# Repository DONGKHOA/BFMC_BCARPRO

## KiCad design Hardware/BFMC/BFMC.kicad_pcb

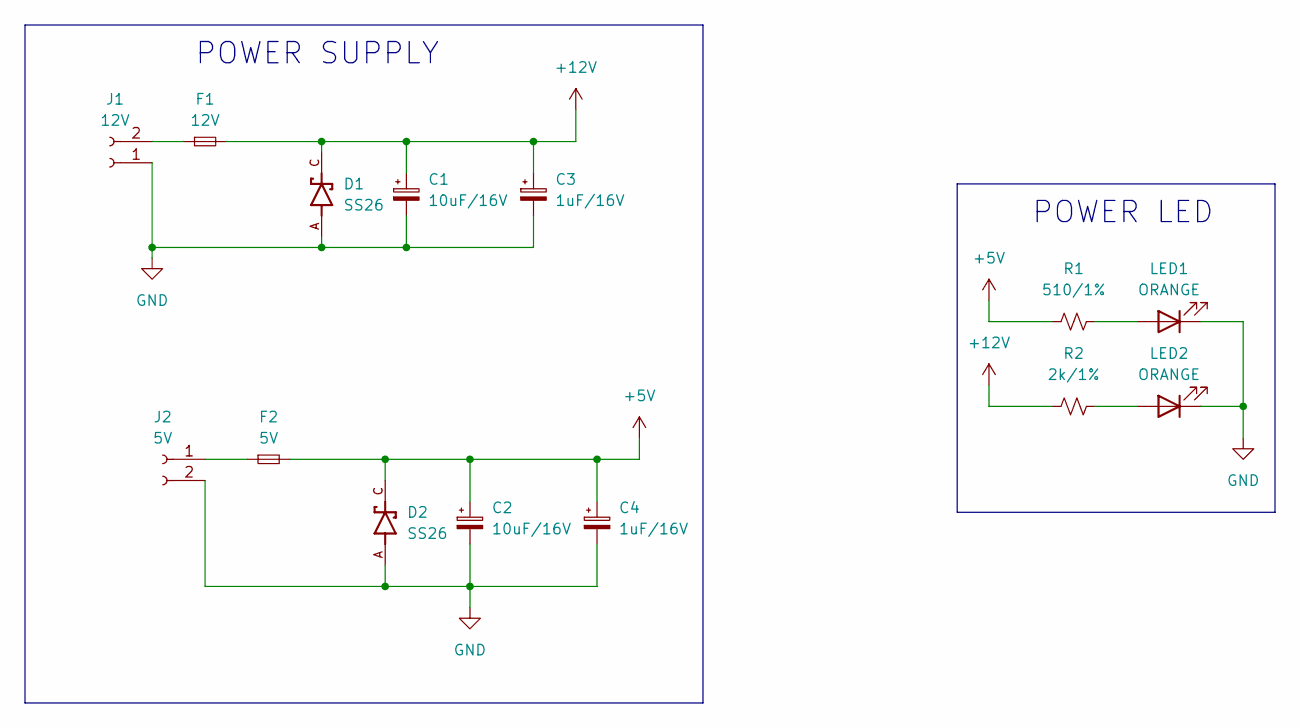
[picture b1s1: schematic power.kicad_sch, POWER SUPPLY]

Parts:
C1, C2: 10uF/16V; CP_Elec_4x5.4
C3, C4: 1uF/16V; CP_Elec_4x5.4
D1, D2: SS26; DIOM4325X250N
F1: 12V; Fuse_1812_4532Metric_Pad1.30x3.40mm_HandSolder
F2: 5V; Fuse_1812_4532Metric_Pad1.30x3.40mm_HandSolder
J1: 12V; au_XH_2.54mm_2_Chan_Dan_SMD_Nam_Ngang
J2: 5V; TerminalBlock_MetzConnect_Type073_RT02602HBLU_1x02_P5.08mm_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
LED1, LED2: ORANGE; LED_1206_3216Metric_Pad1.42x1.75mm_HandSolder
R1: 510/1%; R_0603_1608Metric_Pad0.98x0.95mm_HandSolder
R2: 2k/1%; R_0603_1608Metric_Pad0.98x0.95mm_HandSolder

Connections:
+5V: C2.1, C4.1, D2.C, F2.2, R1.1; also elsewhere on the board
+12V: C1.1, C3.1, D1.C, F1.2, R2.1; also elsewhere on the board
GND: C1.2, C2.2, C3.2, C4.2, D1.A, D2.A, J1.1, J2.2, LED1.1 (K), LED2.1 (K); also elsewhere on the board
unnamed: F1.1, J1.2
unnamed: F2.1, J2.1
unnamed: LED1.2 (A), R1.2
unnamed: LED2.2 (A), R2.2

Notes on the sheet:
POWER SUPPLY
POWER LED

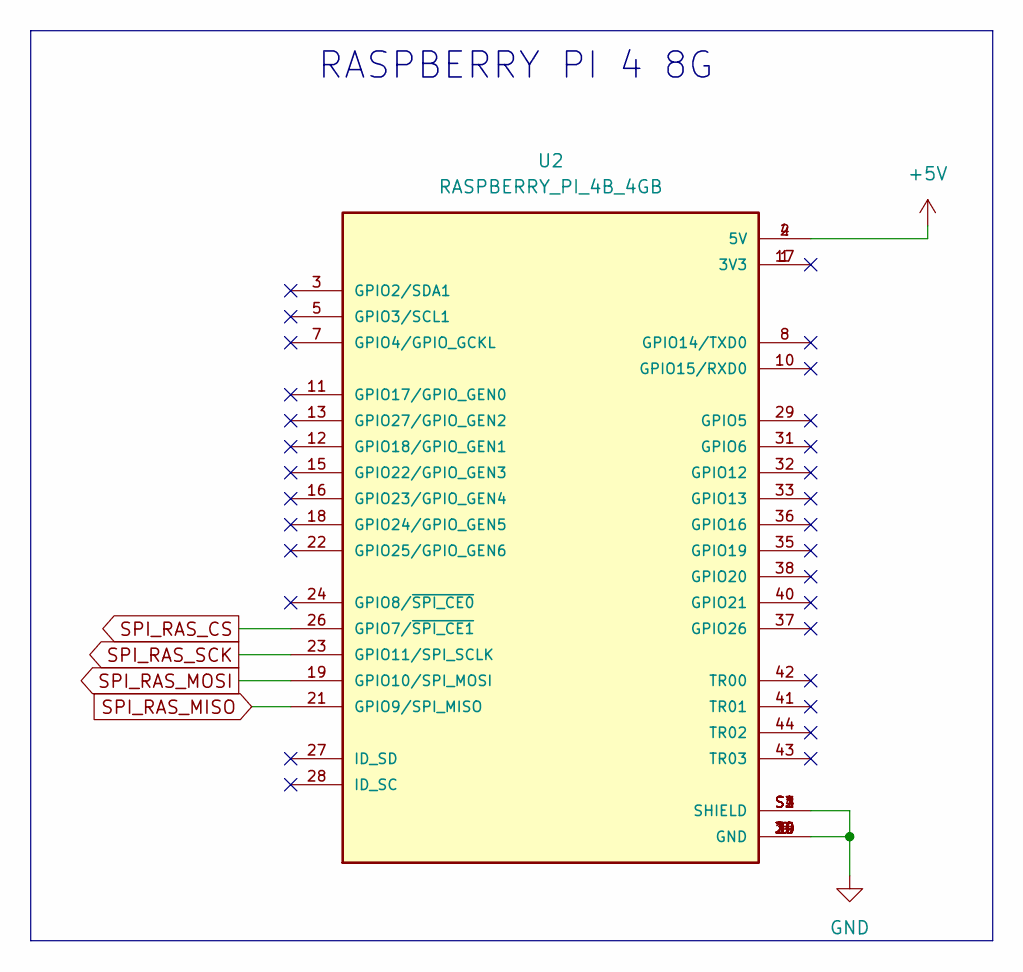
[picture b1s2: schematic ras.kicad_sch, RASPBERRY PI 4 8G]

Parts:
U2: RASPBERRY_PI_4B_4GB; MODULE_RASPBERRY_PI_4B_4GB; PARTREV 4

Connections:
+5V: U2.2 (5V), U2.4 (5V); also elsewhere on the board
GND: U2.6 (GND), U2.9 (GND), U2.14 (GND), U2.20 (GND), U2.25 (GND), U2.30 (GND), U2.34 (GND), U2.39 (GND), U2.S1 (SHIELD), U2.S2 (SHIELD), U2.S3 (SHIELD), U2.S4 (SHIELD); also elsewhere on the board
SPI_RAS_CS: U2.26 (GPIO7/~SPI_CE1); also elsewhere on the board
SPI_RAS_MISO: U2.21 (GPIO9/SPI_MISO); also elsewhere on the board
SPI_RAS_MOSI: U2.19 (GPIO10/SPI_MOSI); also elsewhere on the board
SPI_RAS_SCK: U2.23 (GPIO11/SPI_SCLK); also elsewhere on the board

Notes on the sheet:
RASPBERRY PI 4 8G

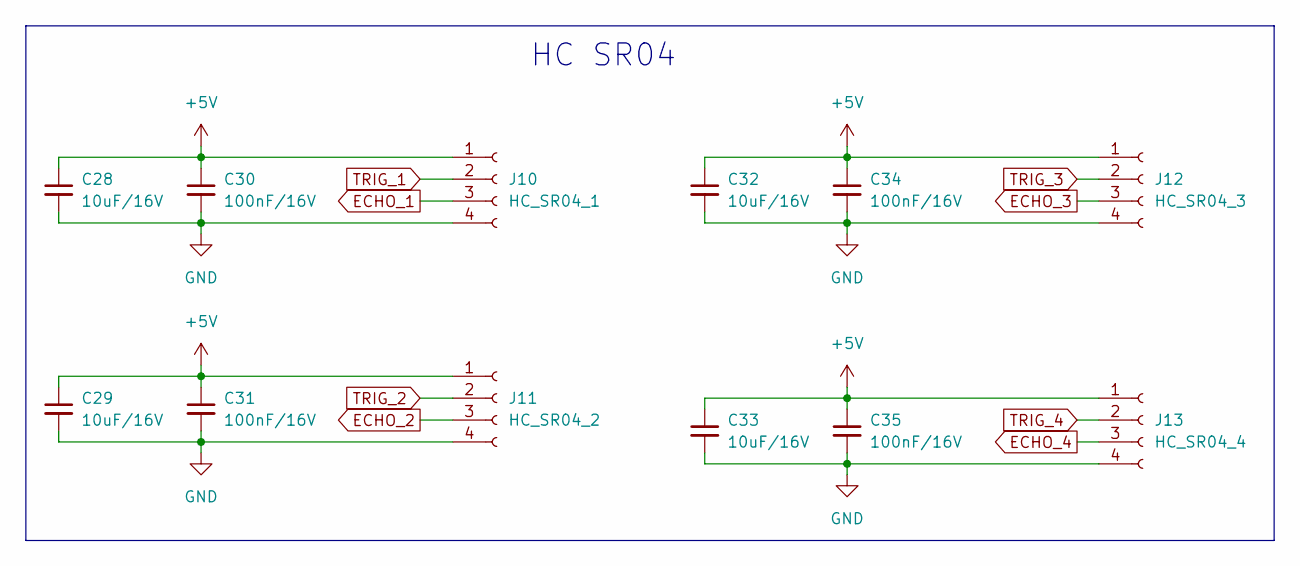
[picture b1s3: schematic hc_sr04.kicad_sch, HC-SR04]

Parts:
C28, C29, C32, C33: 10uF/16V; C_0603_1608Metric_Pad1.08x0.95mm_HandSolder
C30, C31, C34, C35: 100nF/16V; C_0603_1608Metric_Pad1.08x0.95mm_HandSolder
J10: HC_SR04_1; au_XH_2.54mm_4_Chan_Dan_SMD_Nam_Ngang
J11: HC_SR04_2; au_XH_2.54mm_4_Chan_Dan_SMD_Nam_Ngang
J12: HC_SR04_3; au_XH_2.54mm_4_Chan_Dan_SMD_Nam_Ngang
J13: HC_SR04_4; au_XH_2.54mm_4_Chan_Dan_SMD_Nam_Ngang

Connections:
+5V: C28.1, C29.1, C30.1, C31.1, C32.1, C33.1, C34.1, C35.1, J10.1, J11.1, J12.1, J13.1; also elsewhere on the board
ECHO_1: J10.3; also elsewhere on the board
ECHO_2: J11.3; also elsewhere on the board
ECHO_3: J12.3; also elsewhere on the board
ECHO_4: J13.3; also elsewhere on the board
GND: C28.2, C29.2, C30.2, C31.2, C32.2, C33.2, C34.2, C35.2, J10.4, J11.4, J12.4, J13.4; also elsewhere on the board
TRIG_1: J10.2; also elsewhere on the board
TRIG_2: J11.2; also elsewhere on the board
TRIG_3: J12.2; also elsewhere on the board
TRIG_4: J13.2; also elsewhere on the board

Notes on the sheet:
HC SR04

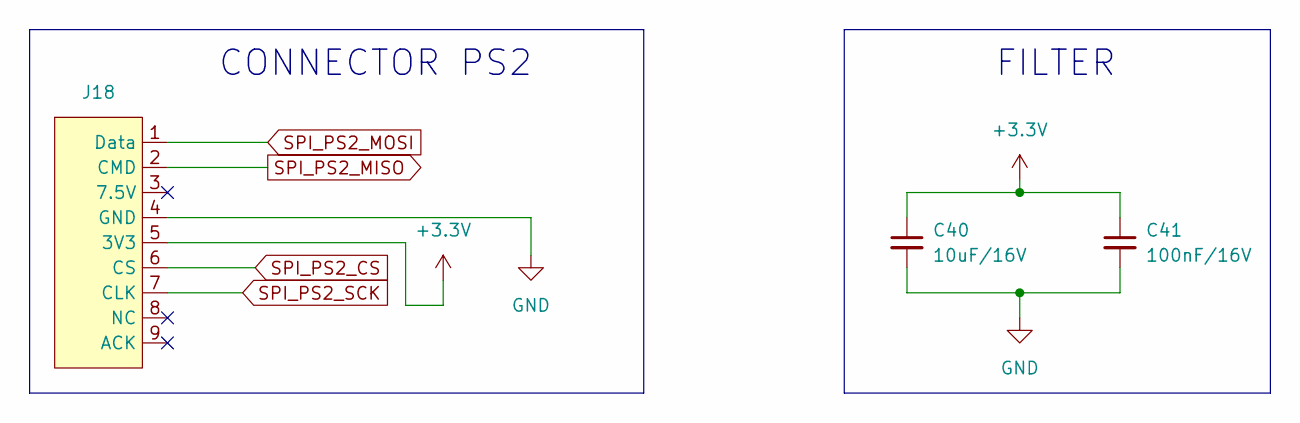
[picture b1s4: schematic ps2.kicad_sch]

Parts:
C40: 10uF/16V; C_0603_1608Metric_Pad1.08x0.95mm_HandSolder
C41: 100nF/16V; C_0603_1608Metric_Pad1.08x0.95mm_HandSolder
J18: jack_ps2

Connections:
+3.3V: C40.1, C41.1, J18.5 (3V3); also elsewhere on the board
GND: C40.2, C41.2, J18.4 (GND); also elsewhere on the board
SPI_PS2_CS: J18.6 (CS); also elsewhere on the board
SPI_PS2_MISO: J18.2 (CMD); also elsewhere on the board
SPI_PS2_MOSI: J18.1 (Data); also elsewhere on the board
SPI_PS2_SCK: J18.7 (CLK); also elsewhere on the board

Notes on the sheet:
CONNECTOR PS2
FILTER

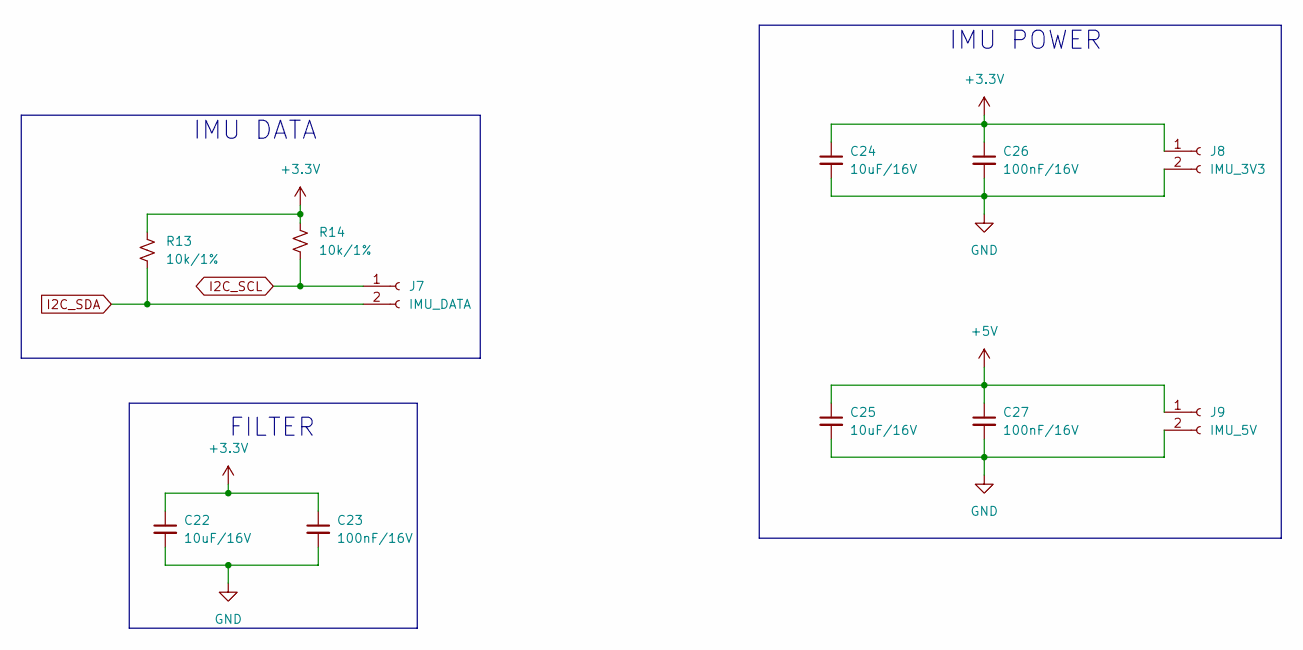
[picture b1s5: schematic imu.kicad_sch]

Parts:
C22, C24, C25: 10uF/16V; C_0603_1608Metric_Pad1.08x0.95mm_HandSolder
C23, C26, C27: 100nF/16V; C_0603_1608Metric_Pad1.08x0.95mm_HandSolder
J7: IMU_DATA; au_XH_2.54mm_2_Chan_Dan_SMD_Nam_Ngang
J8: IMU_3V3; au_XH_2.54mm_2_Chan_Dan_SMD_Nam_Ngang
J9: IMU_5V; au_XH_2.54mm_2_Chan_Dan_SMD_Nam_Ngang
R13, R14: 10k/1%; R_0603_1608Metric_Pad0.98x0.95mm_HandSolder

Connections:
+3.3V: C22.1, C23.1, C24.1, C26.1, J8.1, R13.1, R14.1; also elsewhere on the board
+5V: C25.1, C27.1, J9.1; also elsewhere on the board
GND: C22.2, C23.2, C24.2, C25.2, C26.2, C27.2, J8.2, J9.2; also elsewhere on the board
I2C_SCL: J7.1, R14.2; also elsewhere on the board
I2C_SDA: J7.2, R13.2; also elsewhere on the board

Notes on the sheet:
IMU POWER
IMU DATA
FILTER

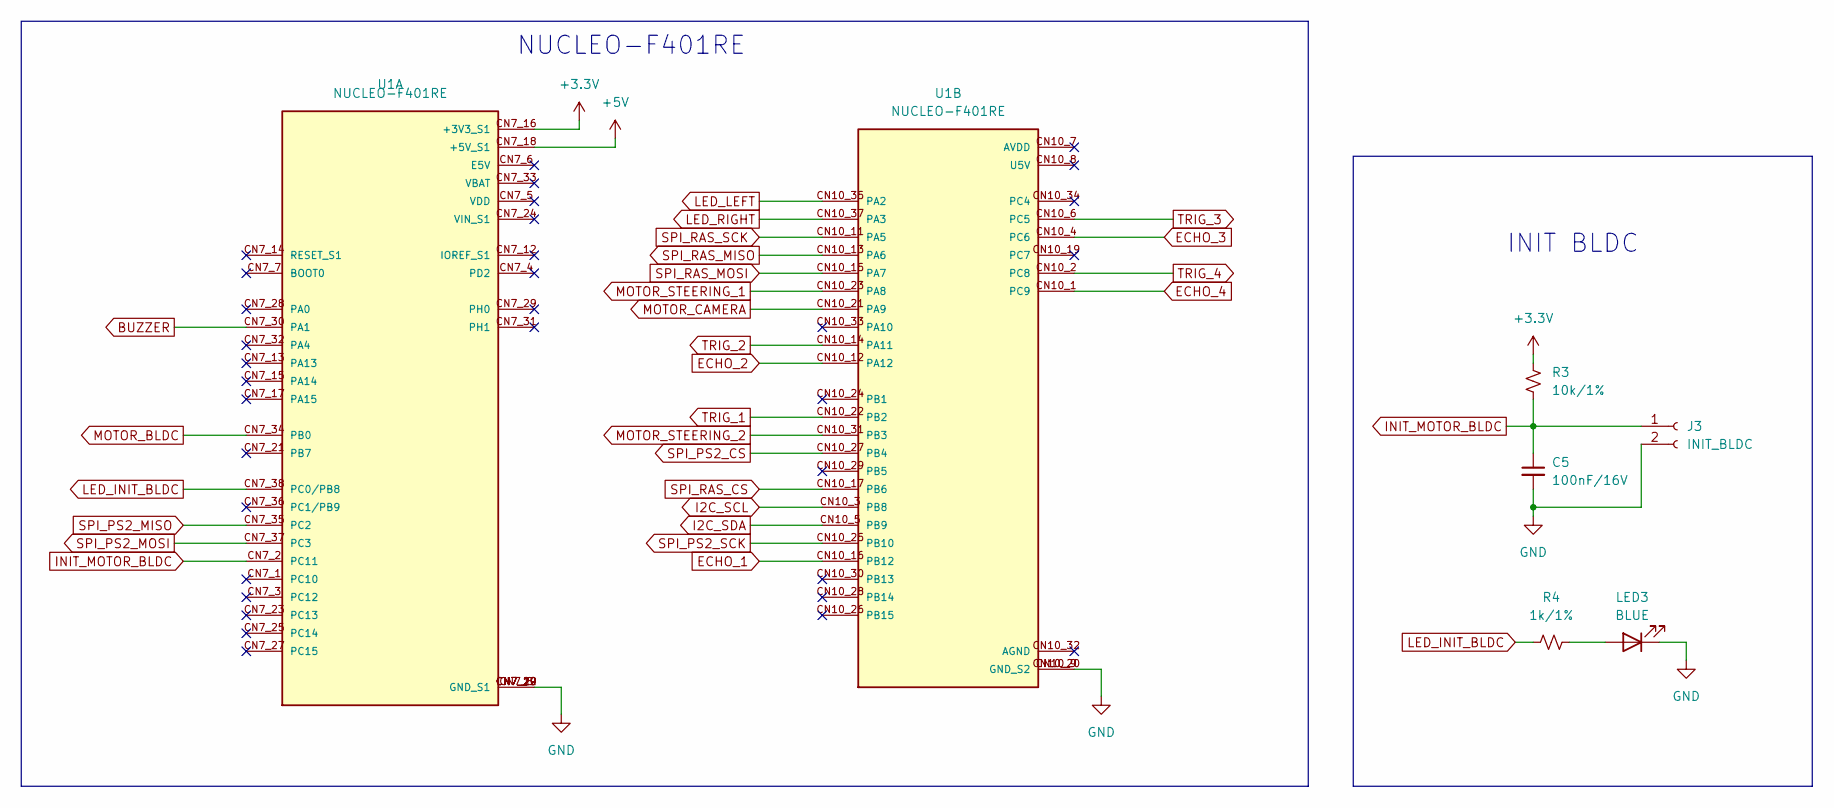
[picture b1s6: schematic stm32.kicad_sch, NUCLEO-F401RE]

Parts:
C5: 100nF/16V; C_0603_1608Metric_Pad1.08x0.95mm_HandSolder
J3: INIT_BLDC; au_XH_2.54mm_2_Chan_Dan_SMD_Nam_Ngang
LED3: BLUE; LED_1206_3216Metric_Pad1.42x1.75mm_HandSolder
R3: 10k/1%; R_0603_1608Metric_Pad0.98x0.95mm_HandSolder
R4: 1k/1%; R_0603_1608Metric_Pad0.98x0.95mm_HandSolder
U1: NUCLEO-F401RE; ST_NUCLEO-F401RE; PARTREV 13

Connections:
+3.3V: R3.1, U1.CN7_16 (+3V3_S1); also elsewhere on the board
+5V: U1.CN7_18 (+5V_S1); also elsewhere on the board
BUZZER: U1.CN7_30 (PA1); also elsewhere on the board
ECHO_1: U1.CN10_16 (PB12); also elsewhere on the board
ECHO_2: U1.CN10_12 (PA12); also elsewhere on the board
ECHO_3: U1.CN10_4 (PC6); also elsewhere on the board
ECHO_4: U1.CN10_1 (PC9); also elsewhere on the board
GND: C5.2, J3.2, LED3.1 (K), U1.CN7_8 (GND_S1), U1.CN7_19 (GND_S1), U1.CN7_20 (GND_S1), U1.CN7_22 (GND_S1), U1.CN10_9 (GND_S2), U1.CN10_20 (GND_S2); also elsewhere on the board
I2C_SCL: U1.CN10_3 (PB8); also elsewhere on the board
I2C_SDA: U1.CN10_5 (PB9); also elsewhere on the board
INIT_MOTOR_BLDC: C5.1, J3.1, R3.2, U1.CN7_2 (PC11)
LED_INIT_BLDC: R4.1, U1.CN7_38 (PC0/PB8)
LED_LEFT: U1.CN10_35 (PA2); also elsewhere on the board
LED_RIGHT: U1.CN10_37 (PA3); also elsewhere on the board
MOTOR_BLDC: U1.CN7_34 (PB0); also elsewhere on the board
MOTOR_CAMERA: U1.CN10_21 (PA9); also elsewhere on the board
MOTOR_STEERING_1: U1.CN10_23 (PA8); also elsewhere on the board
MOTOR_STEERING_2: U1.CN10_31 (PB3); also elsewhere on the board
unnamed: LED3.2 (A), R4.2
SPI_PS2_CS: U1.CN10_27 (PB4); also elsewhere on the board
SPI_PS2_MISO: U1.CN7_35 (PC2); also elsewhere on the board
SPI_PS2_MOSI: U1.CN7_37 (PC3); also elsewhere on the board
SPI_PS2_SCK: U1.CN10_25 (PB10); also elsewhere on the board
SPI_RAS_CS: U1.CN10_17 (PB6); also elsewhere on the board
SPI_RAS_MISO: U1.CN10_13 (PA6); also elsewhere on the board
SPI_RAS_MOSI: U1.CN10_15 (PA7); also elsewhere on the board
SPI_RAS_SCK: U1.CN10_11 (PA5); also elsewhere on the board
TRIG_1: U1.CN10_22 (PB2); also elsewhere on the board
TRIG_2: U1.CN10_14 (PA11); also elsewhere on the board
TRIG_3: U1.CN10_6 (PC5); also elsewhere on the board
TRIG_4: U1.CN10_2 (PC8); also elsewhere on the board

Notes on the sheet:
INIT BLDC
NUCLEO-F401RE

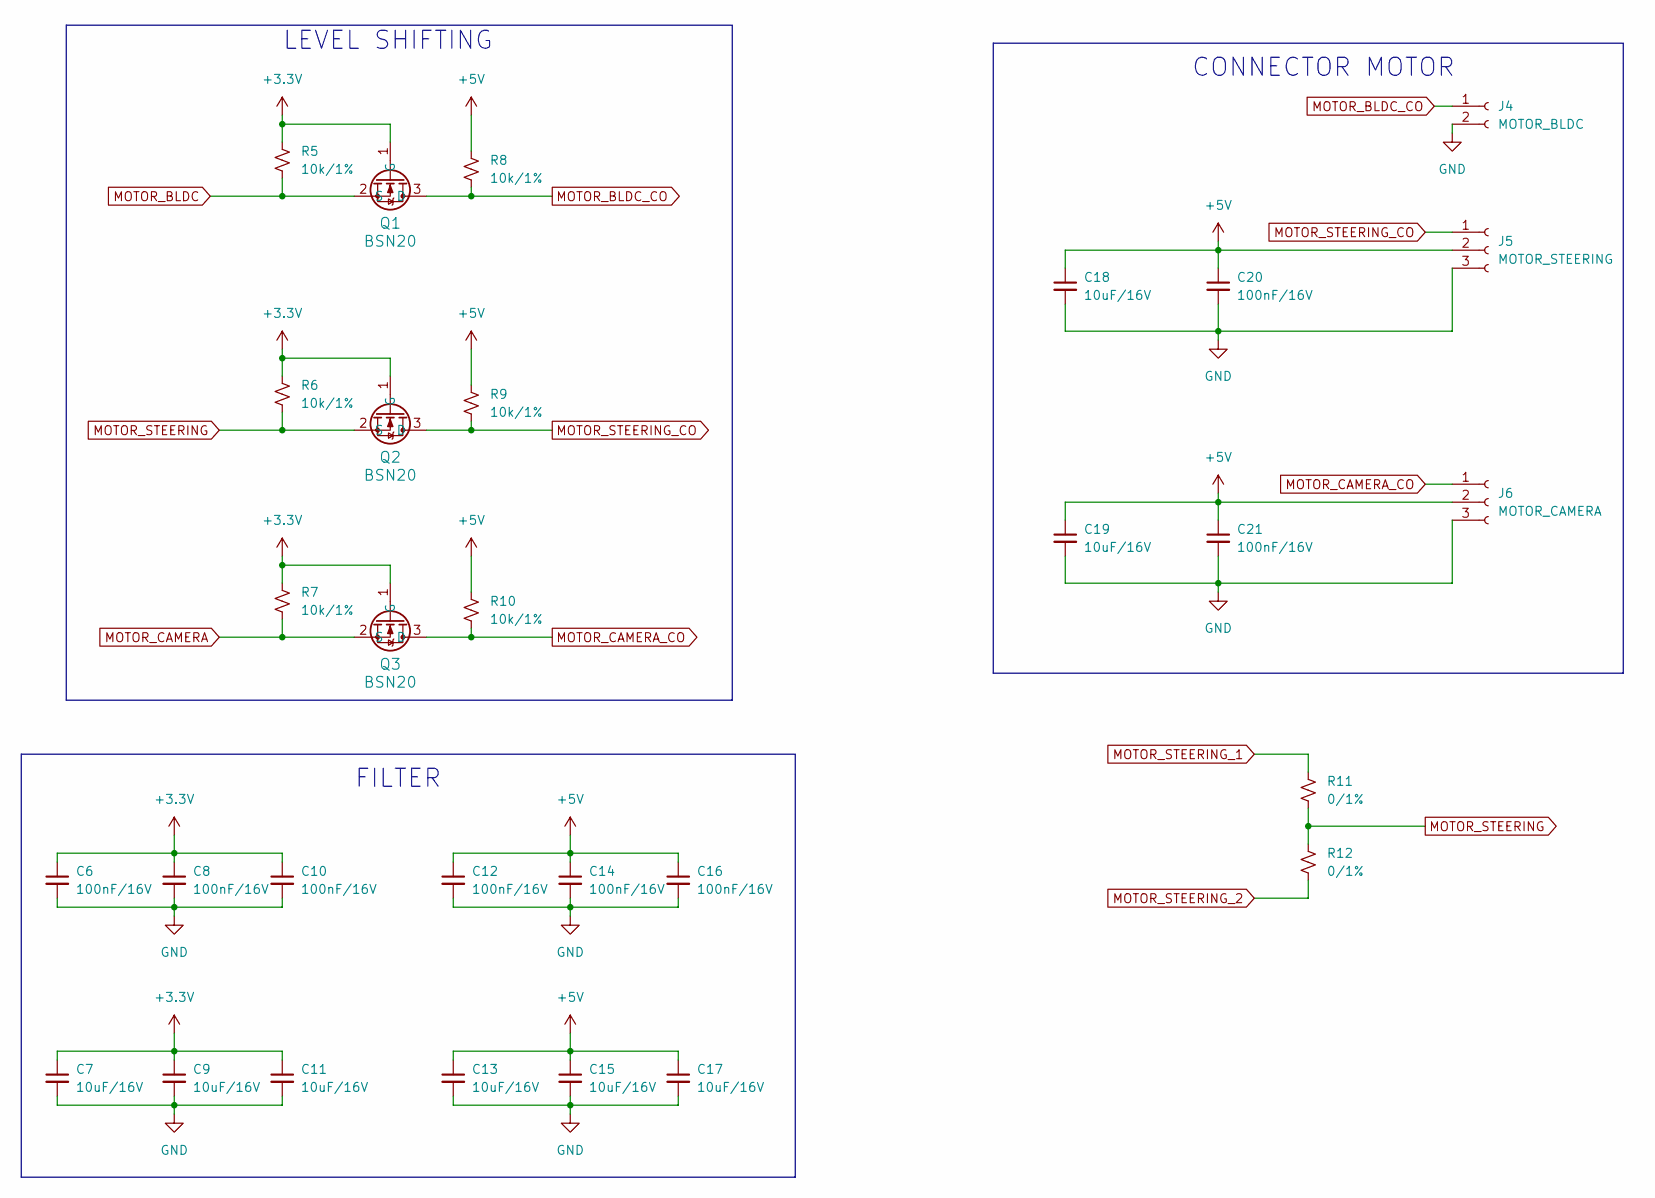
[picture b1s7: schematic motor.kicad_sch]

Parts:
C6, C8, C10, C12, C14, C16, C20, C21: 100nF/16V; C_0603_1608Metric_Pad1.08x0.95mm_HandSolder
C7, C9, C11, C13, C15, C17, C18, C19: 10uF/16V; C_0603_1608Metric_Pad1.08x0.95mm_HandSolder
J4: MOTOR_BLDC; au_XH_2.54mm_2_Chan_Dan_SMD_Nam_Ngang
J5: MOTOR_STEERING; PinHeader_1x03_P2.54mm_Horizontal
J6: MOTOR_CAMERA; PinHeader_1x03_P2.54mm_Horizontal
Q1, Q2, Q3: BSN20; SOT23_NEX
R5, R6, R7, R8, R9, R10: 10k/1%; R_0603_1608Metric_Pad0.98x0.95mm_HandSolder
R11, R12: 0/1%; R_0603_1608Metric_Pad0.98x0.95mm_HandSolder

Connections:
+3.3V: C6.1, C7.1, C8.1, C9.1, C10.1, C11.1, Q1.1 (G), Q2.1 (G), Q3.1 (G), R5.1, R6.1, R7.1; also elsewhere on the board
+5V: C12.1, C13.1, C14.1, C15.1, C16.1, C17.1, C18.1, C19.1, C20.1, C21.1, J5.2, J6.2, R8.1, R9.1, R10.1; also elsewhere on the board
GND: C6.2, C7.2, C8.2, C9.2, C10.2, C11.2, C12.2, C13.2, C14.2, C15.2, C16.2, C17.2, C18.2, C19.2, C20.2, C21.2, J4.2, J5.3, J6.3; also elsewhere on the board
MOTOR_BLDC: Q1.2 (S), R5.2; also elsewhere on the board
MOTOR_BLDC_CO: J4.1, Q1.3 (D), R8.2
MOTOR_CAMERA: Q3.2 (S), R7.2; also elsewhere on the board
MOTOR_CAMERA_CO: J6.1, Q3.3 (D), R10.2
MOTOR_STEERING: Q2.2 (S), R6.2, R11.2, R12.1
MOTOR_STEERING_1: R11.1; also elsewhere on the board
MOTOR_STEERING_2: R12.2; also elsewhere on the board
MOTOR_STEERING_CO: J5.1, Q2.3 (D), R9.2

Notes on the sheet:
LEVEL SHIFTING
CONNECTOR MOTOR
FILTER

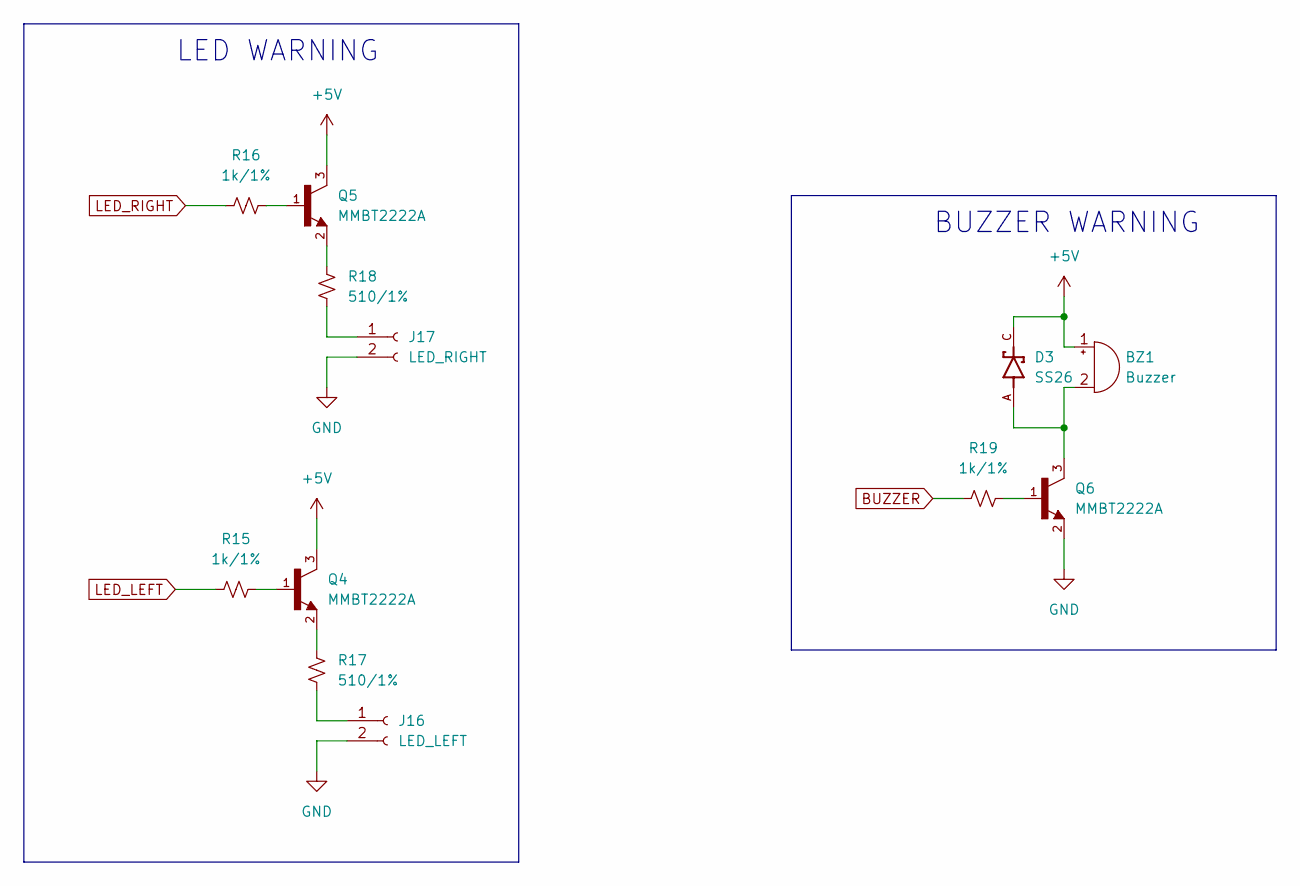
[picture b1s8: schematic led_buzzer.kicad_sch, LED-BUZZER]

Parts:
BZ1: Buzzer; Buzzer_12x9.5RM7.6
D3: SS26; DIOM4325X250N
J16: LED_LEFT; au_XH_2.54mm_2_Chan_Dan_SMD_Nam_Ngang
J17: LED_RIGHT; au_XH_2.54mm_2_Chan_Dan_SMD_Nam_Ngang
Q4, Q5, Q6: MMBT2222A; SOT23
R15, R16, R19: 1k/1%; R_0603_1608Metric_Pad0.98x0.95mm_HandSolder
R17, R18: 510/1%; R_0603_1608Metric_Pad0.98x0.95mm_HandSolder

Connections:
+5V: BZ1.1 (-), D3.C, Q4.3, Q5.3; also elsewhere on the board
BUZZER: R19.1; also elsewhere on the board
GND: J16.2, J17.2, Q6.2; also elsewhere on the board
LED_LEFT: R15.1; also elsewhere on the board
LED_RIGHT: R16.1; also elsewhere on the board
unnamed: BZ1.2 (+), D3.A, Q6.3
unnamed: J16.1, R17.1
unnamed: J17.1, R18.1
unnamed: Q4.1, R15.2
unnamed: Q4.2, R17.2
unnamed: Q5.1, R16.2
unnamed: Q5.2, R18.2
unnamed: Q6.1, R19.2

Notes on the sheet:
LED WARNING
BUZZER WARNING

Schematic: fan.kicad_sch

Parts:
C36, C37: 100nF/16V; C_0603_1608Metric_Pad1.08x0.95mm_HandSolder
C38, C39: 10uF/16V; C_0603_1608Metric_Pad1.08x0.95mm_HandSolder
J14: FAN_FET; au_XH_2.54mm_2_Chan_Dan_SMD_Nam_Ngang
J15: FAN_RAS; au_XH_2.54mm_2_Chan_Dan_SMD_Nam_Ngang

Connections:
+12V: C36.1, C37.1, C38.1, C39.1, J14.2, J15.2; also elsewhere on the board
GND: C36.2, C37.2, C38.2, C39.2, J14.1, J15.1; also elsewhere on the board

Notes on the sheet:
FAN

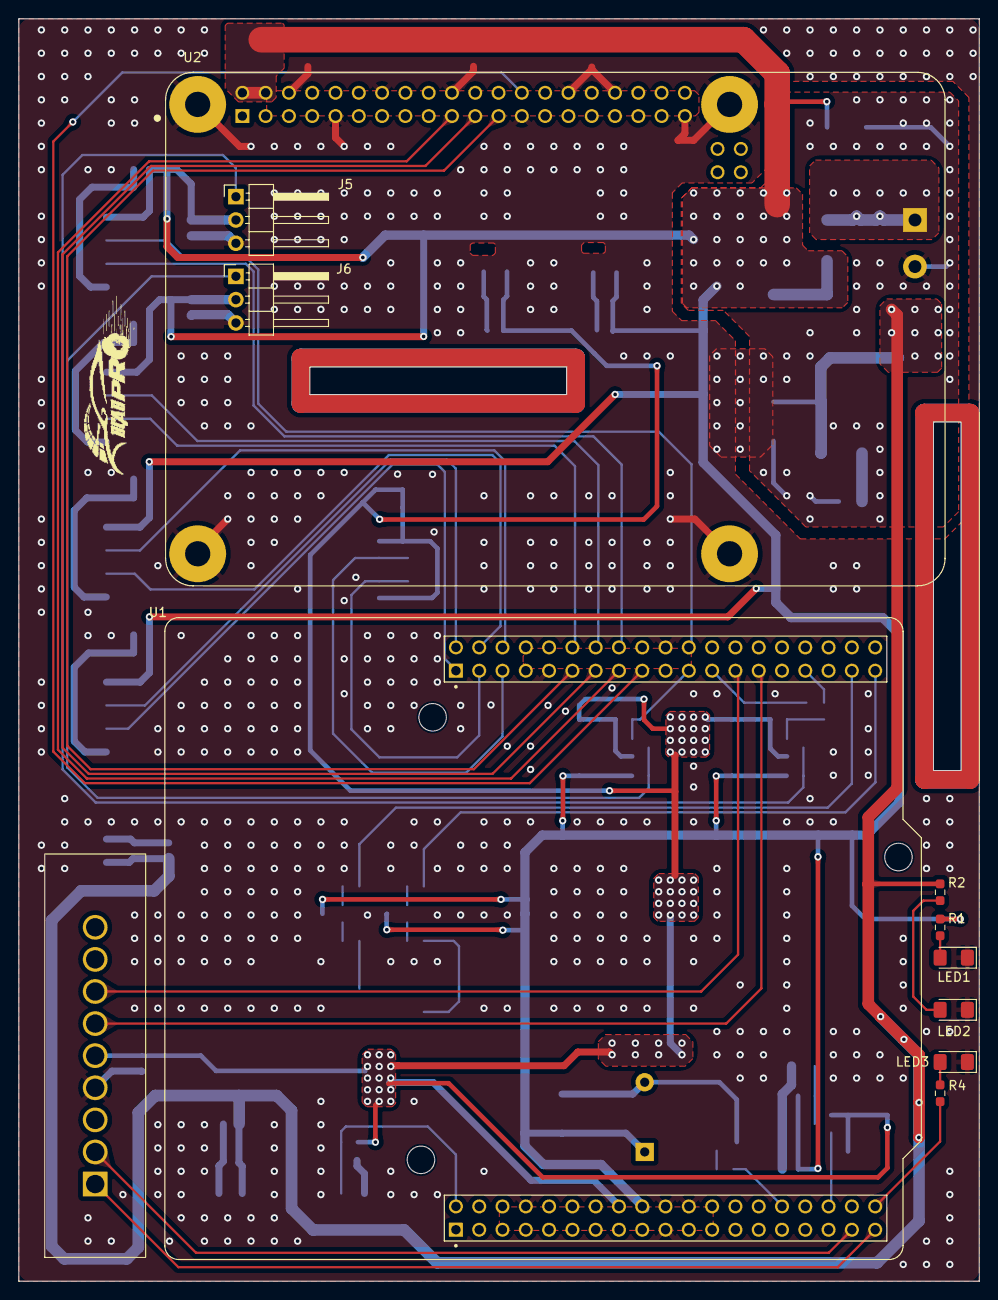
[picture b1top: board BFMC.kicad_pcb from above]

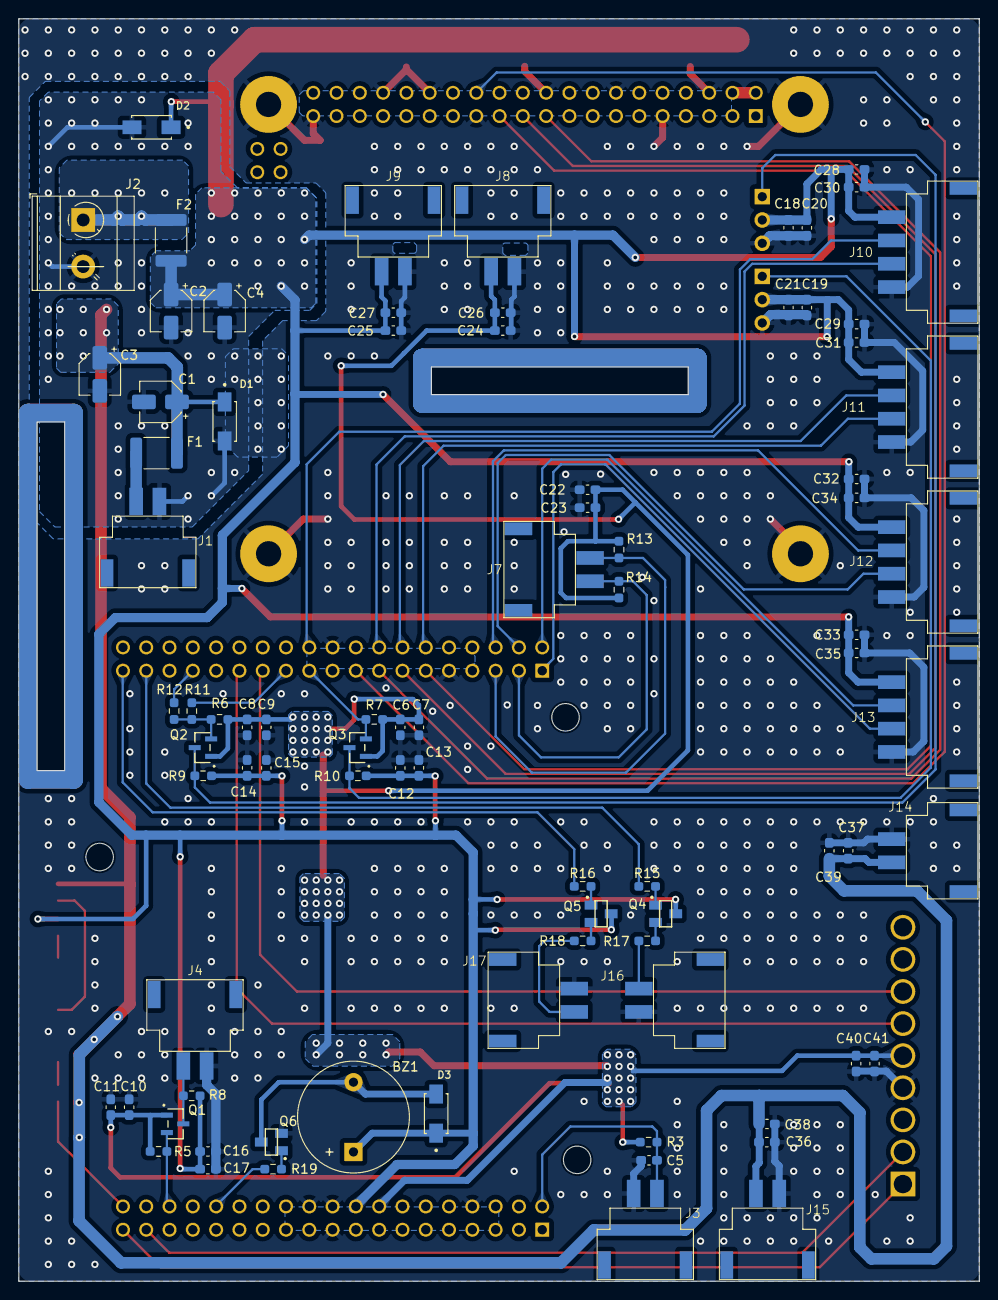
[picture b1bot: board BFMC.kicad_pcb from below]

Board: 2 copper layers, 104.7 x 137.7 mm, 95 parts (84 on the bottom side), 48 nets.

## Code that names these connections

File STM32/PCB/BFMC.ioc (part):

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Mcu.Name=STM32F401R(D-E)Tx
Mcu.Package=LQFP64
Mcu.UserName=STM32F401RETx
PA1.GPIOParameters=GPIO_Label
PA1.GPIO_Label=BUZZER
PA1.Signal=GPIO_Output
PA11.GPIOParameters=GPIO_Label
PA11.GPIO_Label=TRIG_2
PA11.Signal=GPIO_Output
PA12.GPIOParameters=GPIO_Label
PA12.GPIO_Label=ECHO_2
PA12.Signal=GPIO_Input
PA13.Mode=Serial_Wire
PA13.Signal=SYS_JTMS-SWDIO
PA14.Mode=Serial_Wire
PA14.Signal=SYS_JTCK-SWCLK
PA2.GPIOParameters=GPIO_Label
PA2.GPIO_Label=LED_LEFT
PA2.Signal=GPIO_Output
PA3.GPIOParameters=GPIO_Label
PA3.GPIO_Label=LED_RIGHT
PA3.Signal=GPIO_Output
PA5.GPIOParameters=GPIO_Label
PA5.GPIO_Label=SPI_RAS_SCK
PA5.Mode=Full_Duplex_Slave
PA5.Signal=SPI1_SCK
PA6.GPIOParameters=GPIO_Label
PA6.GPIO_Label=SPI_RAS_MISO
PA6.Mode=Full_Duplex_Slave
PA6.Signal=SPI1_MISO
PA7.GPIOParameters=GPIO_Label
PA7.GPIO_Label=SPI_RAS_MOSI
PA7.Mode=Full_Duplex_Slave
PA7.Signal=SPI1_MOSI
PA8.GPIOParameters=GPIO_Label
PA8.GPIO_Label=MOTOR_STEERING
PA8.Signal=S_TIM1_CH1
PA9.GPIOParameters=GPIO_Label
PA9.GPIO_Label=MOTOR_CAM
PA9.Signal=S_TIM1_CH2
PB0.GPIOParameters=GPIO_Label
PB0.GPIO_Label=MOTOR_BLDC
PB0.Signal=S_TIM3_CH3
PB10.GPIOParameters=GPIO_Label
PB10.GPIO_Label=SPI_PS2_SCK
PB10.Mode=Full_Duplex_Slave
PB10.Signal=SPI2_SCK
PB12.GPIOParameters=GPIO_Label
PB12.GPIO_Label=ECHO_1
PB12.Signal=GPIO_Input
PB2.GPIOParameters=GPIO_Label
PB2.GPIO_Label=TRIG_1
PB2.Signal=GPIO_Output
PB4.GPIOParameters=GPIO_Label
PB4.GPIO_Label=SPI_PS2_CS
PB4.Signal=GPIO_Output
PB6.GPIOParameters=GPIO_Label
PB6.GPIO_Label=SPI_RAS_CS
PB6.Signal=GPIO_Input
PB8.Mode=I2C
PB8.Signal=I2C1_SCL
PB9.Mode=I2C
PB9.Signal=I2C1_SDA
PC0.GPIOParameters=GPIO_Label
PC0.GPIO_Label=LED_INIT_BLDC
PC0.Signal=GPIO_Output
PC1.GPIOParameters=GPIO_Label
PC1.GPIO_Label=INIT_BLDC
PC1.Signal=GPIO_Input
PC2.GPIOParameters=GPIO_Label
PC2.GPIO_Label=SPI_PS2_MISO
PC2.Mode=Full_Duplex_Slave
PC2.Signal=SPI2_MISO
PC3.GPIOParameters=GPIO_Label
PC3.GPIO_Label=SPI_PS2_MOSI
PC3.Mode=Full_Duplex_Slave
PC3.Signal=SPI2_MOSI
PC5.GPIOParameters=GPIO_Label
PC5.GPIO_Label=TRIG_3
PC5.Signal=GPIO_Output
PC6.GPIOParameters=GPIO_Label
PC6.GPIO_Label=ECHO_3
PC6.Signal=GPIO_Input
PC8.GPIOParameters=GPIO_Label
PC8.GPIO_Label=TRIG_4
PC8.Signal=GPIO_Output
PC9.GPIOParameters=GPIO_Label
PC9.GPIO_Label=ECHO_4
PC9.Signal=GPIO_Input
PH0\ -\ OSC_IN.Mode=HSE-External-Clock-Source
PH0\ -\ OSC_IN.Signal=RCC_OSC_IN
PH1\ -\ OSC_OUT.Mode=HSE-External-Clock-Source
PH1\ -\ OSC_OUT.Signal=RCC_OSC_OUT
RCC.HSE_VALUE=25000000
RCC.SYSCLKFreq_VALUE=70000000
RCC.SYSCLKSource=RCC_SYSCLKSOURCE_PLLCLK
board=custom

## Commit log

2023-11-20 update by khoa
2023-11-20 update by thkhoa
2023-11-20 update by minh
2023-11-20 update by Thinh
2023-11-22 minhdeptrai
2023-11-22 update_22/11
2023-11-22 22_11
2023-11-24 main update by khoa dong, add folder Study C++
2023-11-24 update by khoa dong
2023-11-24 update by khoa dong, update folder study c++
2023-11-24 update by khoa dong, branch main
2023-11-24 upload study c++
2023-11-27 upload dectect sign
2023-11-27 Update by Thinh 27/11/2023
2023-11-27 test commit xoa cmt
2023-11-30 update linh tinh 30/11
2023-12-01 upload stm32 tree folder
2023-12-01 update stm32 tree folder
2023-12-01 update stm32
2023-12-01 update file python
2023-12-01 up test
2024-01-14 BitterSweet
2024-01-14 restructure folder
2024-01-15 updated 1501 by thkhoa
2024-01-17 thkhoa
2024-01-17 upload tree folder
2024-01-17 add comment function
2024-01-17 tkhoa
2024-01-17 update vo tri
2024-01-17 update driver
2024-01-22 updated by thkhoa
2024-01-24 21_01
2024-01-24 anhminh
2024-01-29 update main
2024-02-01 update Firmware Stm32
2024-02-01 update STM32 setup file
2024-02-01 update tree file in stm32 testboard
2024-02-01 update temporary file in stm32
2024-02-02 fix: update lib button, delay_timer, hc_sr04
2024-02-04 Thinh test
2024-02-06 thkhoa up
2024-02-07 Update distance_handle
2024-02-08 bug:imu, servo
2024-02-11 update imu_app
2024-02-13 fix: format document
2024-02-13 THinh update
2024-02-14 thkhoa - fix: cmt & format
2024-02-14 add: file in app lib
2024-02-15 thkhoa - style: delete cmts
2024-02-26 fix: update mpu9050 addr
2024-02-26 fix: update mpu6050.c
2024-02-26 fix: mpu
2024-02-29 feat: update ps2
2024-02-29 fix: ps2
2024-02-29 temp
2024-02-29 fix:ps2: update state
2024-03-02 control_steering
2024-03-02 push PID
2024-03-02 feature:ps2:updte funtion button
2024-03-02 fix:all: fix syntax
2024-03-02 driver camera motor
2024-03-02 update zo tri
2024-03-02 fix:imu: revcovery
2024-03-02 code:maic.c: update thread, spi
2024-03-02 code:main.c: add queue spi
2024-03-02 code:debug.h: change from define DEBUG to DEBUG_USER
2024-03-02 Xóa tệp không cần thiết
2024-03-02 Tạo thư mục lane_detection
2024-03-02 Lane_detection_version1
2024-03-02 update Control Steering
2024-03-03 code:situation: add function controlCar...
2024-03-03 code:main,bldc: preliminary update
2024-03-04 bosch brain
2024-03-04 code:ain, situation: update all thread
2024-03-04 code:ain: update interrupt
2024-03-04 feat: add spi_controll & interrupt spi
2024-03-04 code:lib/app: delete spi control
2024-03-05 fix: spi interrupt
2024-03-06 update ps2
2024-03-06 Thinh update code
2024-03-06 fix: change spi variables
